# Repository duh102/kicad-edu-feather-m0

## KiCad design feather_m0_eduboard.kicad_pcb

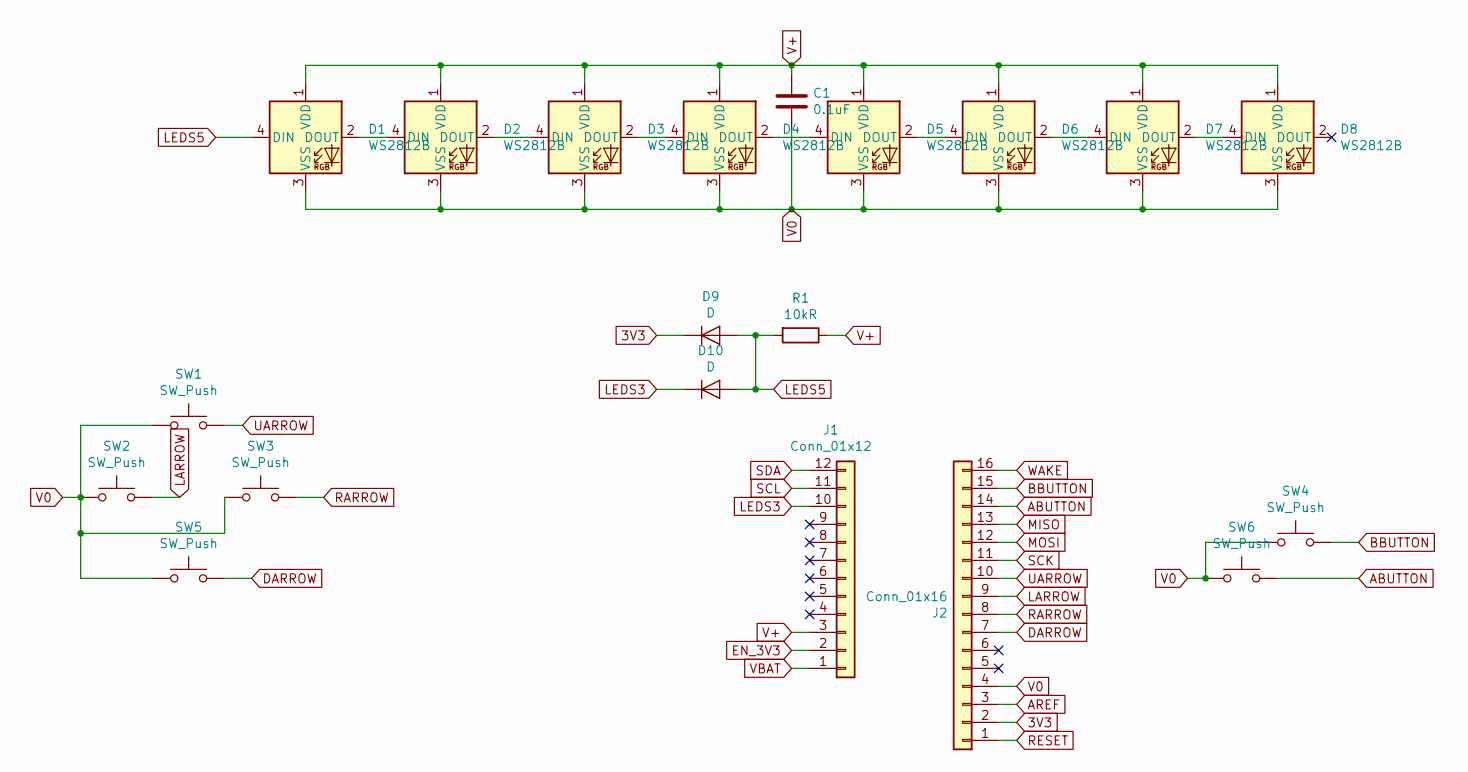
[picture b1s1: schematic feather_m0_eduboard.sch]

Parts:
C1: 0.1uF; C_0603_1608Metric
D1, D2, D3, D4, D5, D6, D7, D8: WS2812B; LED_WS2812B_PLCC4_5.0x5.0mm_P3.2mm
D9, D10: D; D_SOD-323F
J1: Conn_01x12; PinSocket_1x12_P2.54mm_Vertical
J2: Conn_01x16; PinSocket_1x16_P2.54mm_Vertical
R1: 10kR; R_0603_1608Metric
SW1, SW2, SW3, SW4, SW5, SW6: SW_Push; SW_SPST_TL3342

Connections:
3V3: D9.1 (K), J2.2
ABUTTON: J2.14, SW6.2; also elsewhere on the board
AREF: J2.3
BBUTTON: J2.15, SW4.2; also elsewhere on the board
DARROW: J2.7, SW5.2
EN_3V3: J1.2
LARROW: J2.9, SW2.2
LEDS3: D10.1 (K), J1.10
LEDS5: D1.4 (DIN), D9.2 (A), D10.2 (A), R1.2
MISO: J2.13
MOSI: J2.12
unnamed: D1.2 (DOUT), D2.4 (DIN)
unnamed: D2.2 (DOUT), D3.4 (DIN)
unnamed: D3.2 (DOUT), D4.4 (DIN)
unnamed: D4.2 (DOUT), D5.4 (DIN)
unnamed: D5.2 (DOUT), D6.4 (DIN)
unnamed: D6.2 (DOUT), D7.4 (DIN)
unnamed: D7.2 (DOUT), D8.4 (DIN)
RARROW: J2.8, SW3.2
RESET: J2.1
SCK: J2.11
SCL: J1.11
SDA: J1.12
UARROW: J2.10, SW1.2
V0: C1.2, D1.3 (VSS), D2.3 (VSS), D3.3 (VSS), D4.3 (VSS), D5.3 (VSS), D6.3 (VSS), D7.3 (VSS), D8.3 (VSS), J2.4, SW1.1, SW2.1, SW3.1, SW4.1, SW5.1, SW6.1; also elsewhere on the board
V+: C1.1, D1.1 (VDD), D2.1 (VDD), D3.1 (VDD), D4.1 (VDD), D5.1 (VDD), D6.1 (VDD), D7.1 (VDD), D8.1 (VDD), J1.3, R1.1
VBAT: J1.1
WAKE: J2.16

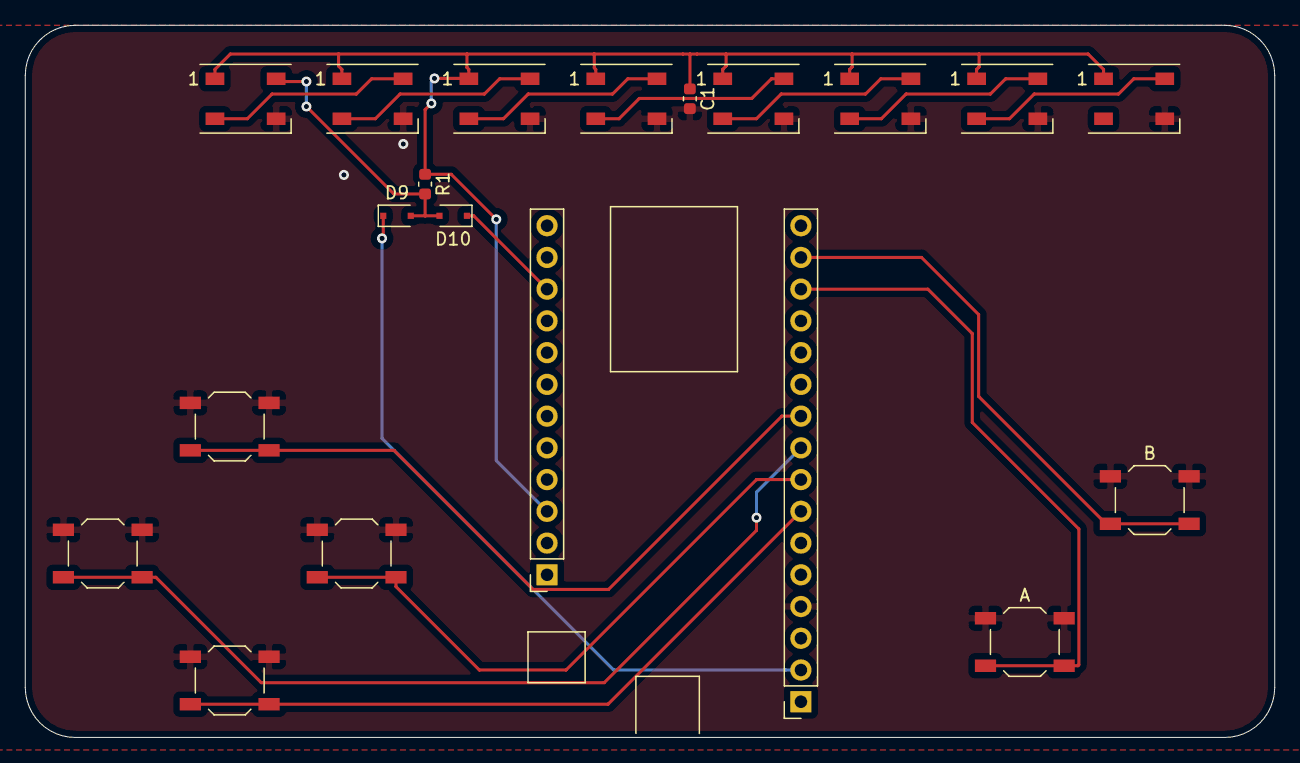
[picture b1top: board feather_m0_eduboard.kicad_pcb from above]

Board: 2 copper layers, 100.0 x 57.0 mm, 20 parts (0 on the bottom side), 18 nets.

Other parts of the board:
A: SW_Push; SW_SPST_TL3342
B: SW_Push; SW_SPST_TL3342

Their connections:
ABUTTON: A.2; also elsewhere on the board
BBUTTON: B.2; also elsewhere on the board
V0: A.1, B.1; also elsewhere on the board
